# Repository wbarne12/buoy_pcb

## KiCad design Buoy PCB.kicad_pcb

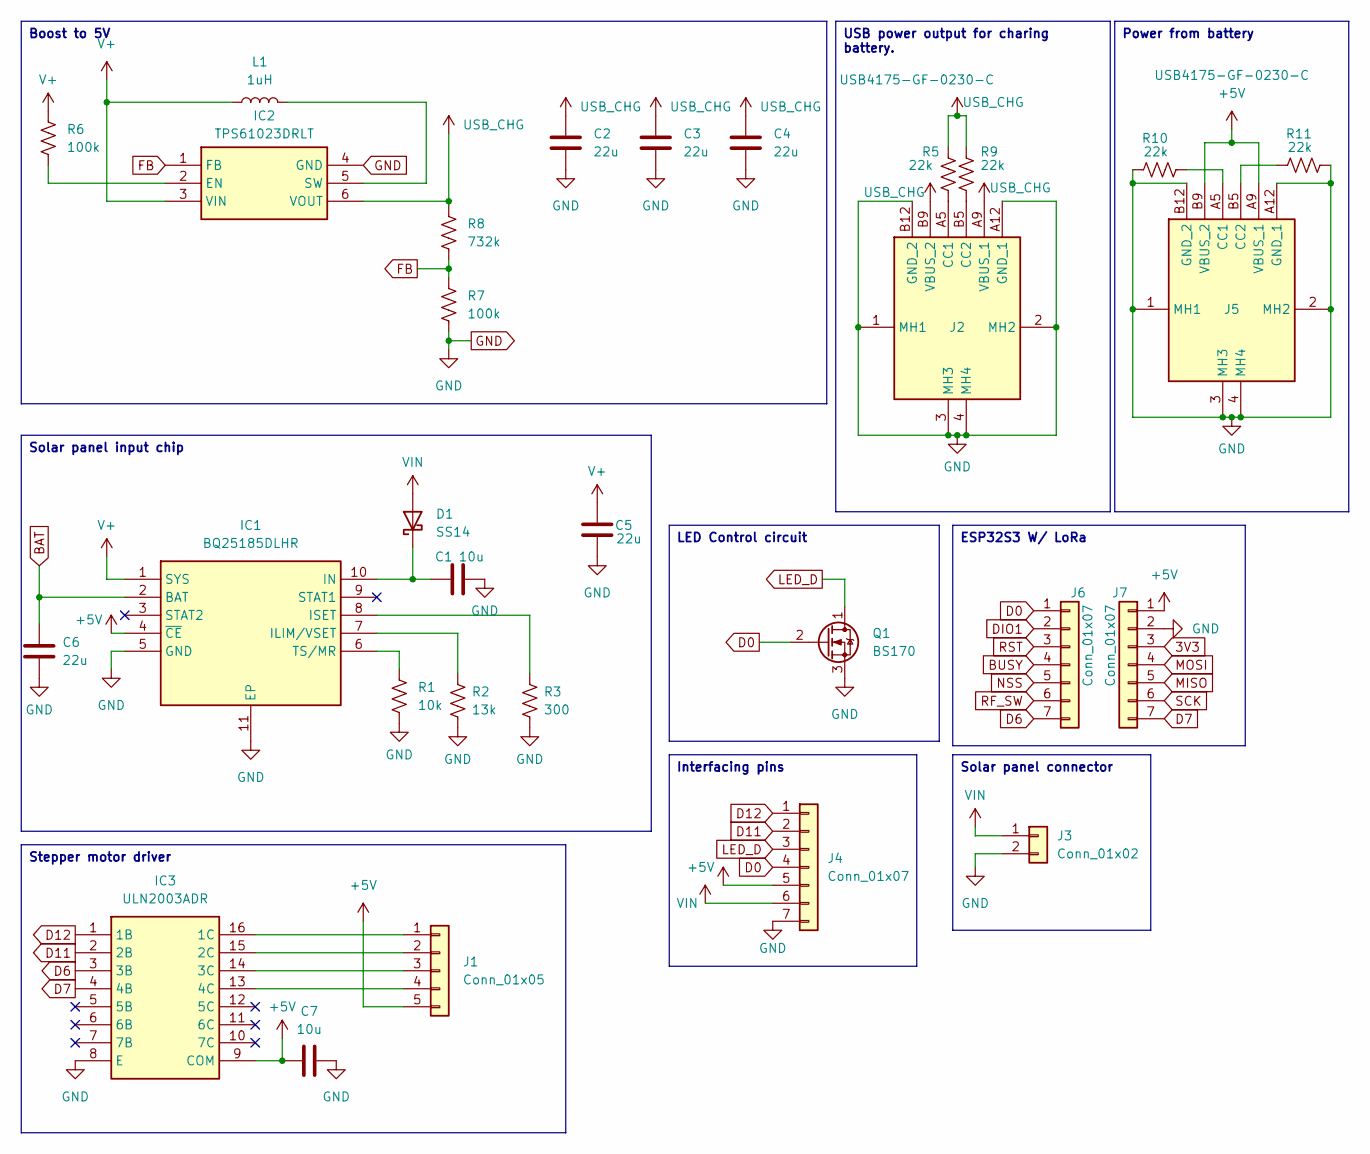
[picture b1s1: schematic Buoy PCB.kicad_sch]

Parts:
C1, C7: 10u; C_1206_3216Metric_Pad1.33x1.80mm_HandSolder
C2, C3, C4, C5, C6: 22u; C_1206_3216Metric_Pad1.33x1.80mm_HandSolder
D1: SS14; D_1206_3216Metric
IC1: BQ25185DLHR; SON40P220X200X80-11N; Mouser Part Number 595-BQ25185DLHR
IC2: TPS61023DRLT; SOTFL50P160X60-6N; Mouser Part Number 595-TPS61023DRLT
IC3: ULN2003ADR; SOIC127P600X175-16N; Mouser Part Number 595-ULN2003ADR
J1: Conn_01x05; JST_XH_B5B-XH-AM_1x05_P2.50mm_Vertical
J2, J5: USB4175-GF-0230-C; USB4175GF0230C; Mouser Part Number 640-USB4175-GF-0230C
J3: Conn_01x02; JST_PH_B2B-PH-K_1x02_P2.00mm_Vertical
J4: Conn_01x07; PinHeader_1x07_P2.54mm_Vertical
J6, J7: Conn_01x07; PinSocket_1x07_P2.54mm_Vertical
L1: 1uH; L_1206_3216Metric_Pad1.22x1.90mm_HandSolder
Q1: BS170; TO-92_Inline
R1: 10k; R_1206_3216Metric_Pad1.30x1.75mm_HandSolder
R2: 13k; R_1206_3216Metric_Pad1.30x1.75mm_HandSolder
R3: 300; R_1206_3216Metric_Pad1.30x1.75mm_HandSolder
R5, R9, R10, R11: 22k; R_1206_3216Metric_Pad1.30x1.75mm_HandSolder
R6, R7: 100k; R_1206_3216Metric_Pad1.30x1.75mm_HandSolder
R8: 732k; R_1206_3216Metric_Pad1.30x1.75mm_HandSolder

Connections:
3V3: J7.3
+5V: C7.1, IC1.4 (~CE), IC3.9 (COM), J1.5, J4.5, J5.A9 (VBUS_1), J5.B9 (VBUS_2), J7.1
BAT: C6.1, IC1.2 (BAT)
BUSY: J6.4
D0: J4.4, J6.1, Q1.2 (G)
D6: IC3.3 (3B), J6.7
D7: IC3.4 (4B), J7.7
D11: IC3.2 (2B), J4.2
D12: IC3.1 (1B), J4.1
DIO1: J6.2
FB: IC2.1 (FB), R7.1, R8.2
GND: C1.2, C2.2, C3.2, C4.2, C5.1, C6.2, C7.2, IC1.5 (GND), IC1.11 (EP), IC2.4 (GND), IC3.8 (E), J2.1 (MH1), J2.2 (MH2), J2.3 (MH3), J2.4 (MH4), J2.A12 (GND_1), J2.B12 (GND_2), J3.2, J4.7, J5.1 (MH1), J5.2 (MH2), J5.3 (MH3), J5.4 (MH4), J5.A12 (GND_1), J5.B12 (GND_2), J7.2, Q1.3 (S), R1.2, R2.2, R3.2, R7.2, R10.1, R11.2
LED_D: J4.3, Q1.1 (D)
MISO: J7.5
MOSI: J7.4
NSS: J6.5
unnamed: C1.1, D1.1 (K), IC1.10 (IN)
unnamed: IC1.7 (ILIM/VSET), R2.1
unnamed: IC1.8 (ISET), R3.1
unnamed: IC1.6 (TS/MR), R1.1
unnamed: IC2.2 (EN), R6.2
unnamed: IC2.5 (SW), L1.2
unnamed: IC3.16 (1C), J1.1
unnamed: IC3.15 (2C), J1.2
unnamed: IC3.14 (3C), J1.3
unnamed: IC3.13 (4C), J1.4
unnamed: J2.A5 (CC1), R5.2
unnamed: J2.B5 (CC2), R9.2
unnamed: J5.A5 (CC1), R10.2
unnamed: J5.B5 (CC2), R11.1
RF_SW: J6.6
RST: J6.3
SCK: J7.6
USB_CHG: C2.1, C3.1, C4.1, IC2.6 (VOUT), J2.A9 (VBUS_1), J2.B9 (VBUS_2), R5.1, R8.1, R9.1
V+: C5.2, IC1.1 (SYS), IC2.3 (VIN), L1.1, R6.1
VIN: D1.2 (A), J3.1, J4.6

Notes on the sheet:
Solar panel input chip
Interfacing pins
Power from battery
Boost to 5V
Stepper motor driver
LED Control circuit
ESP32S3 W/ LoRa
USB power output for charing battery.
Solar panel connector

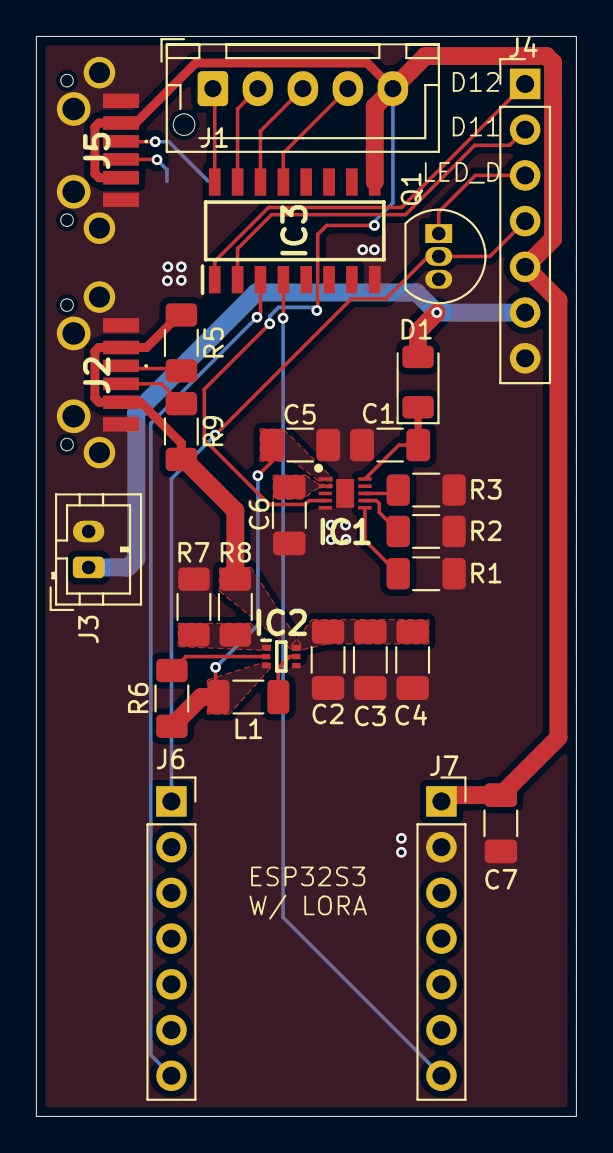
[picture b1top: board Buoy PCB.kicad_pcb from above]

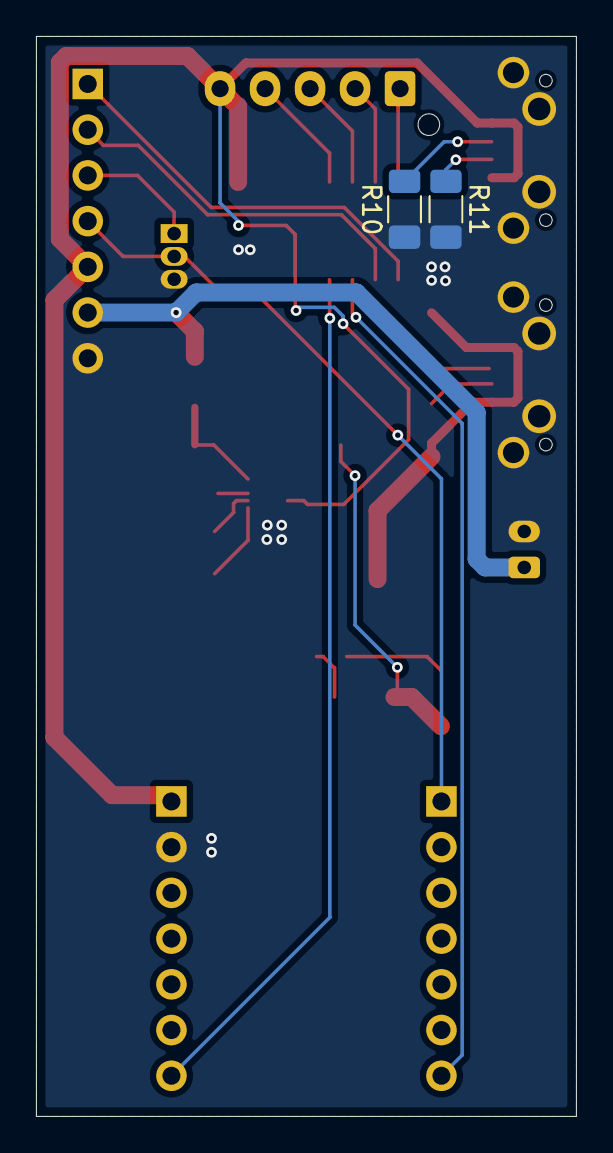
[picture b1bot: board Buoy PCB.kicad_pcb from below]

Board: 2 copper layers, 30.0 x 60.0 mm, 30 parts (2 on the bottom side), 27 nets.

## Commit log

2025-08-05 Added files
